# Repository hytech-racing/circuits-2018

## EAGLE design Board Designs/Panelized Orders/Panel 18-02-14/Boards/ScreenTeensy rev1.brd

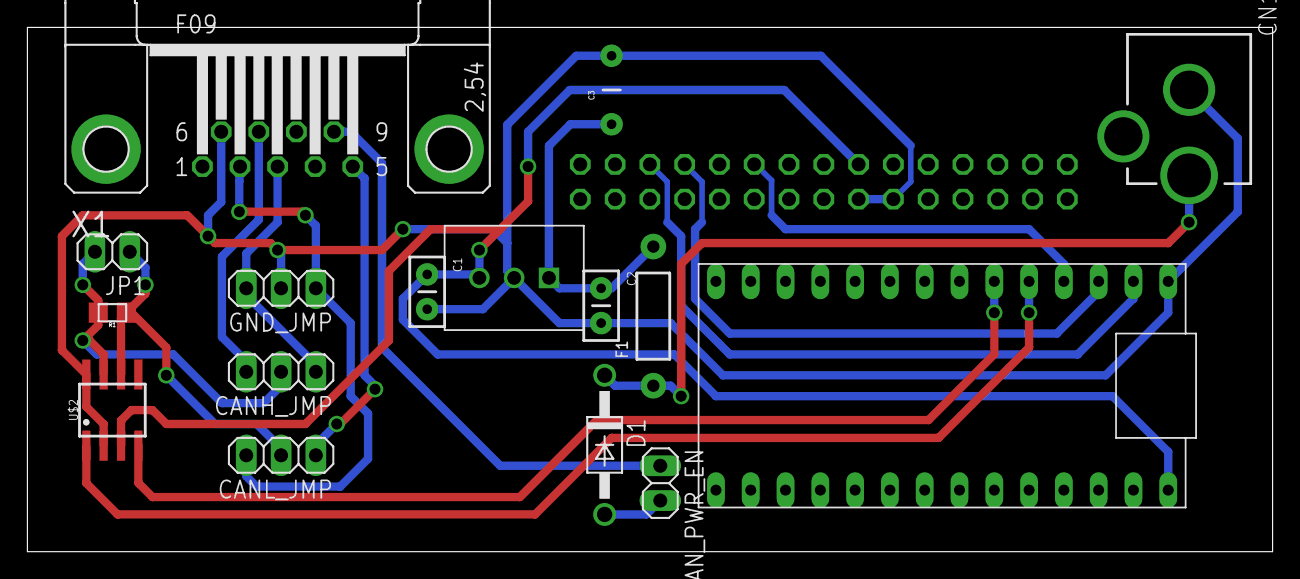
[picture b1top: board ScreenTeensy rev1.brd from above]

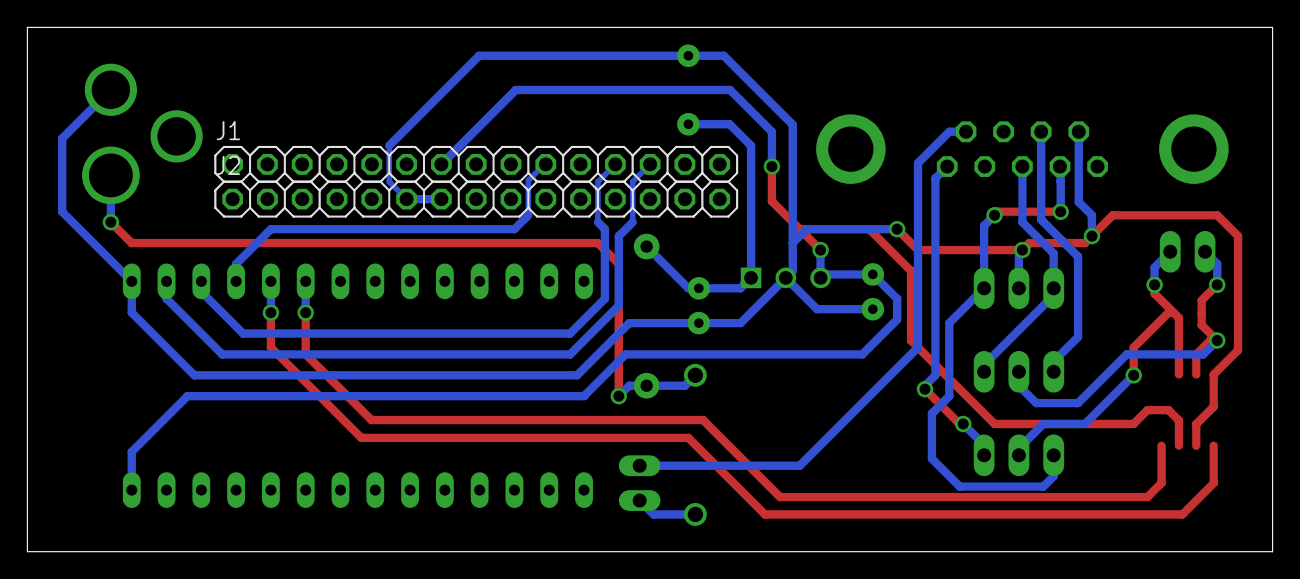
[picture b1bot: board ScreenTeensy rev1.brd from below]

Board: 2 copper layers, 90.9 x 38.3 mm, 18 parts (2 on the bottom side), 17 nets.

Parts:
C1: .1µF; CAP-PTH-SMALLEZ
C2: .33µF; CAP-PTH-SMALLEZ
C3: CAP-PTH-5MM
CANH_JMP: 1X03
CANL_JMP: 1X03
CAN_PWR_EN: 1X02
CN1: DCJACK_2MM_PTH
D1: DIODEDO-41; DO-41
F1: AXIAL-0.4
GND_JMP: 1X03
IC1: TO-220-SPACED
J1, J2: 1X15
JP1: M02; 1X02
R1: 120; 0805
U$1: TEENSY_3.2_SIMPLE
U$2: MCP2551; SOIC-08
X1: F09HP

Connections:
+5V: C1.1, IC1.3, J1.7, U$1.VIN, U$2.3
+12V: C2.1, C3.1, F1.P$2, IC1.1
CANH: CANH_JMP.2, JP1.2, R1.2, U$2.7
CANL: CANL_JMP.2, JP1.1, R1.1, U$2.6
CANRX: U$1.D4(CANRX), U$2.4
CANTX: U$1.D3(CANTX), U$2.1
GND: C1.2, C2.2, C3.2, CN1.GND, GND_JMP.2, IC1.2, J2.6, J2.7, U$1.GND, U$2.2, U$2.8, X1.6
unnamed: CAN_PWR_EN.2, D1.A
unnamed: CAN_PWR_EN.1, X1.9
P2: CANL_JMP.3, GND_JMP.1, X1.2
P3: CANH_JMP.1, GND_JMP.3, X1.3
P5: CANL_JMP.1, X1.5
P7: CANH_JMP.3, X1.7
SCREEN_RS: J1.10, U$1.D2
SCREEN_RX: J1.12, U$1.D1(TX1)
SCREEN_TX: J1.13, U$1.D0(RX1)
V+: CN1.PWR, D1.C, F1.P$1

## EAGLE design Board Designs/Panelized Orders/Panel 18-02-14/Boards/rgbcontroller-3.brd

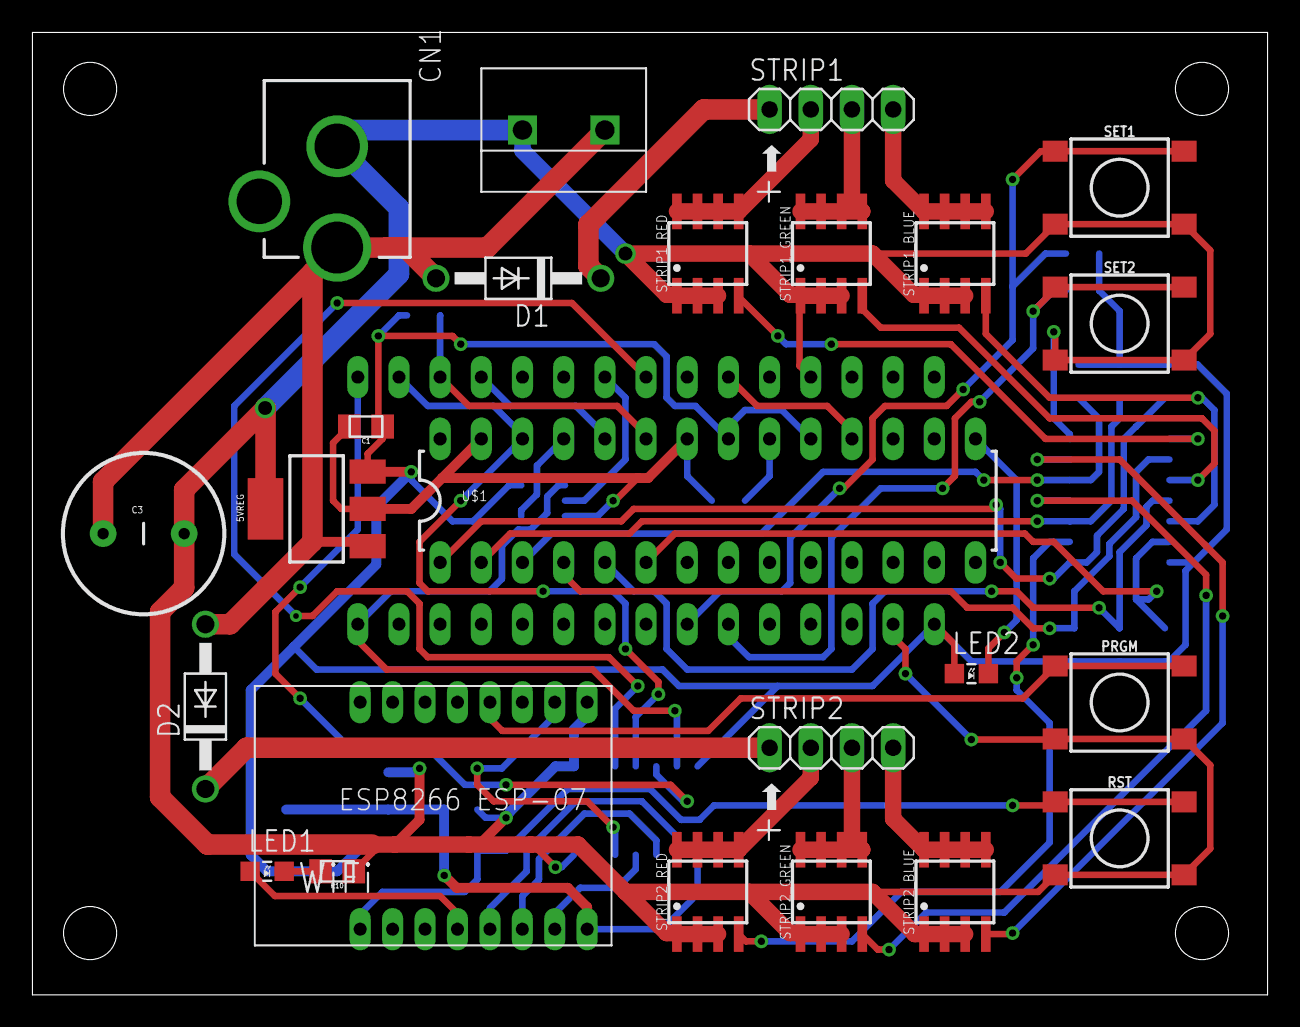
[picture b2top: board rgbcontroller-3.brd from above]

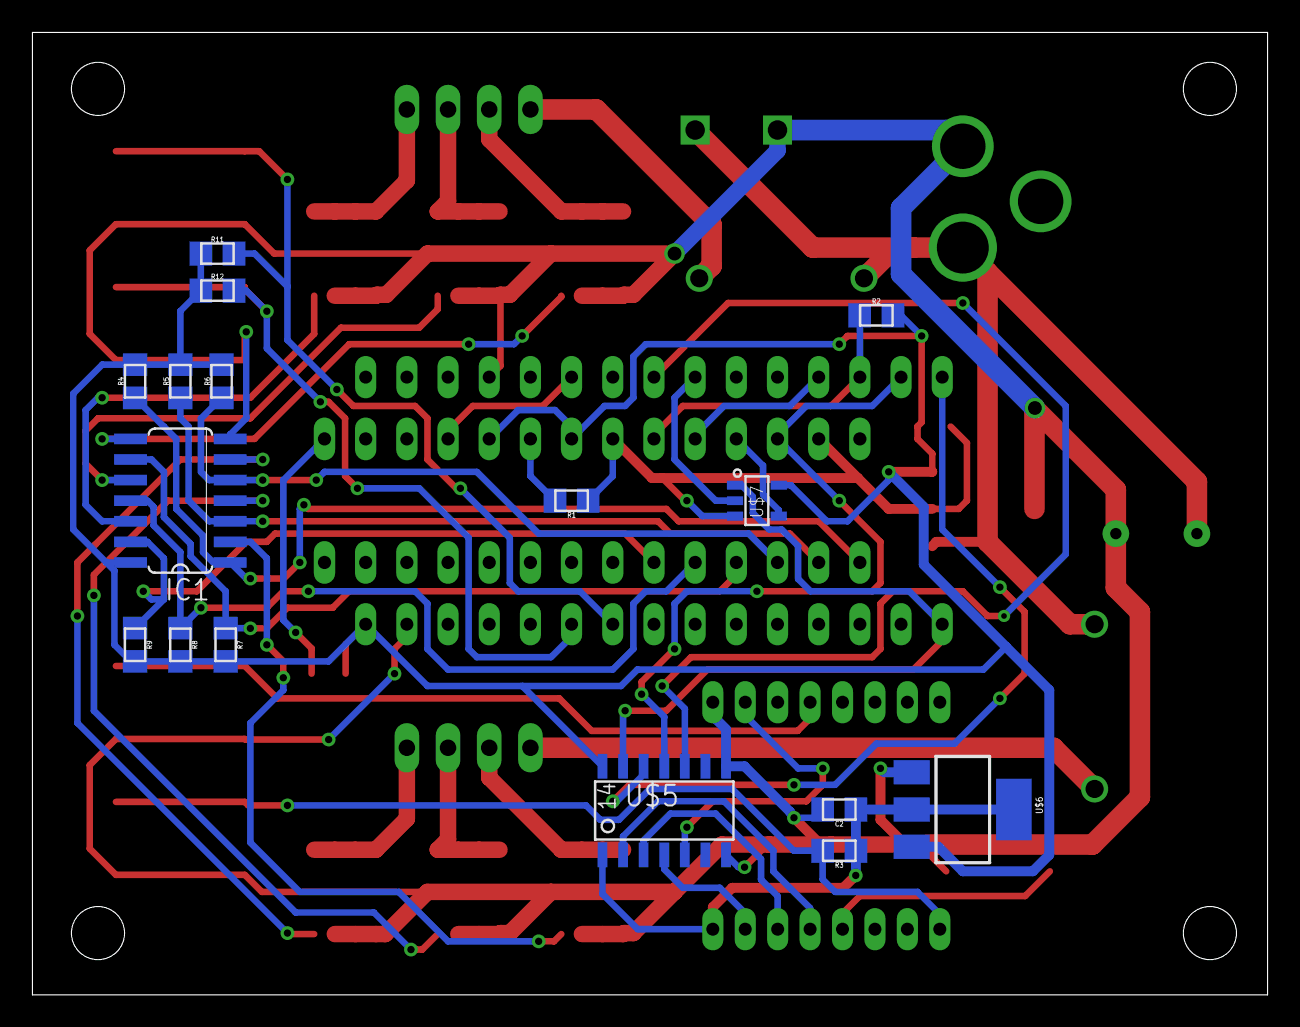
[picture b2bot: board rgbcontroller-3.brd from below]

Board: 2 copper layers, 76.2 x 59.4 mm, 41 parts (16 on the bottom side), 45 nets.

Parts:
5VREG: SOT223
C1: .1µF; 0805
C2: 1µF; 0805
C3: CAP-PTH-5MM
CN1: DCJACK_2MM_PTH
D1, D2: DIODEDO-41; DO-41
IC1: 74HC04D; SO14
LED1: Red; LED-805
LED2: LED-805
PRGM: TACTILE_SWITCH_SMD_6.2MM_TALL
R1: 2.2k; 0805
R2, R3, R4, R5, R6, R7, R8, R9, R11, R12: 10k; 0805
R10: 100; 0805
RST: TACTILE_SWITCH_SMD_6.2MM_TALL
SET1, SET2: TACTILE_SWITCH_SMD_6.2MM_TALL
STRIP1, STRIP2: 1X04
STRIP1_BLUE, STRIP1_GREEN, STRIP1_RED, STRIP2_BLUE, STRIP2_GREEN, STRIP2_RED: MDS1656; SOIC-08
U$1: TLC5940; DIL28-3
U$2: ARDUINO_NANO
U$3: TERMINAL_BLOCK_DG301-02P; DG301-02P
U$4: ESP8266_ESP-07
U$5: SOIC-14
U$6: TLV1117LV33; SOT223
U$7: SN74LVC1G08; SOT-23-5

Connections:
+3V3: C2.1, R3.1, U$4.P$8, U$5.1, U$6.2, U$6.4
+5V: 5VREG.3, C1.1, IC1.14, LED2.A, R2.2, R4.2, R5.2, R6.2, R7.2, R8.2, R9.2, R11.1, R12.1, U$1.19, U$1.21, U$2.VIN, U$5.14, U$6.3, U$7.5
+12V: 5VREG.1, C3.1, CN1.PWR, D1.A, D2.A, U$3.1
BLANK: R2.1, U$1.23, U$2.D10
GND: 5VREG.2, 5VREG.4, C1.2, C2.2, C3.2, CN1.GND, IC1.7, PRGM.A1, PRGM.A2, R1.1, R10.1, RST.A1, RST.A2, SET1.A1, SET1.A2, SET2.A1, SET2.A2, STRIP1_BLUE.1, STRIP1_BLUE.2, STRIP1_BLUE.3, STRIP1_GREEN.1, STRIP1_GREEN.2, STRIP1_GREEN.3, STRIP1_RED.1, STRIP1_RED.2, STRIP1_RED.3, STRIP2_BLUE.1, STRIP2_BLUE.2, STRIP2_BLUE.3, STRIP2_GREEN.1, STRIP2_GREEN.2, STRIP2_GREEN.3, STRIP2_RED.1, STRIP2_RED.2, STRIP2_RED.3, U$1.22, U$1.27, U$2.GND, U$2.GND1, U$3.2, U$4.P$9, U$5.7, U$5.8, U$6.1, U$7.3
MISO: U$2.D12, U$5.12
MISO_33: U$4.P$6, U$5.3
MOSI: U$1.26, U$2.D11, U$5.11
MOSI_33: U$4.P$7, U$5.4
unnamed: STRIP2.2, STRIP2_RED.5, STRIP2_RED.6, STRIP2_RED.7, STRIP2_RED.8
unnamed: STRIP1.2, STRIP1_RED.5, STRIP1_RED.6, STRIP1_RED.7, STRIP1_RED.8
unnamed: IC1.2, STRIP2_RED.4
unnamed: IC1.4, STRIP2_GREEN.4
unnamed: PRGM.B1, PRGM.B2, U$4.P$12
unnamed: R1.2, U$1.20
unnamed: U$1.18, U$2.D3
unnamed: LED1.A, U$4.P$4
unnamed: IC1.8, STRIP1_RED.4
unnamed: IC1.10, STRIP1_GREEN.4
unnamed: IC1.12, STRIP1_BLUE.4
unnamed: IC1.6, STRIP2_BLUE.4
unnamed: IC1.1, R4.1, U$1.1
unnamed: IC1.3, R5.1, U$1.2
unnamed: STRIP1.3, STRIP1_GREEN.5, STRIP1_GREEN.6, STRIP1_GREEN.7, STRIP1_GREEN.8
unnamed: STRIP1.4, STRIP1_BLUE.5, STRIP1_BLUE.6, STRIP1_BLUE.7, STRIP1_BLUE.8
unnamed: STRIP2.3, STRIP2_GREEN.5, STRIP2_GREEN.6, STRIP2_GREEN.7, STRIP2_GREEN.8
unnamed: STRIP2.4, STRIP2_BLUE.5, STRIP2_BLUE.6, STRIP2_BLUE.7, STRIP2_BLUE.8
unnamed: IC1.5, R6.1, U$1.3
unnamed: IC1.13, R9.1, U$1.6
unnamed: R3.2, RST.B1, RST.B2, U$4.P$1
unnamed: IC1.11, R8.1, U$1.5
unnamed: IC1.9, R7.1, U$1.4
unnamed: LED2.C, U$1.15
unnamed: LED1.C, R10.2
unnamed: D1.C, STRIP1.1
unnamed: D2.C, STRIP2.1
SCK: U$2.D13, U$5.13, U$7.1
SCK_33: U$4.P$5, U$5.2
SCK_TLC5940: U$1.25, U$7.4
SET1: R11.2, SET1.B1, SET1.B2, U$2.A5
SET2: R12.2, SET2.B1, SET2.B2, U$2.A6
SS_ESP8266: U$2.D5, U$5.10
SS_ESP8266_33: U$4.P$10, U$5.5
SS_TLC5940: U$2.D6, U$7.2
XLAT: U$1.24, U$2.D9

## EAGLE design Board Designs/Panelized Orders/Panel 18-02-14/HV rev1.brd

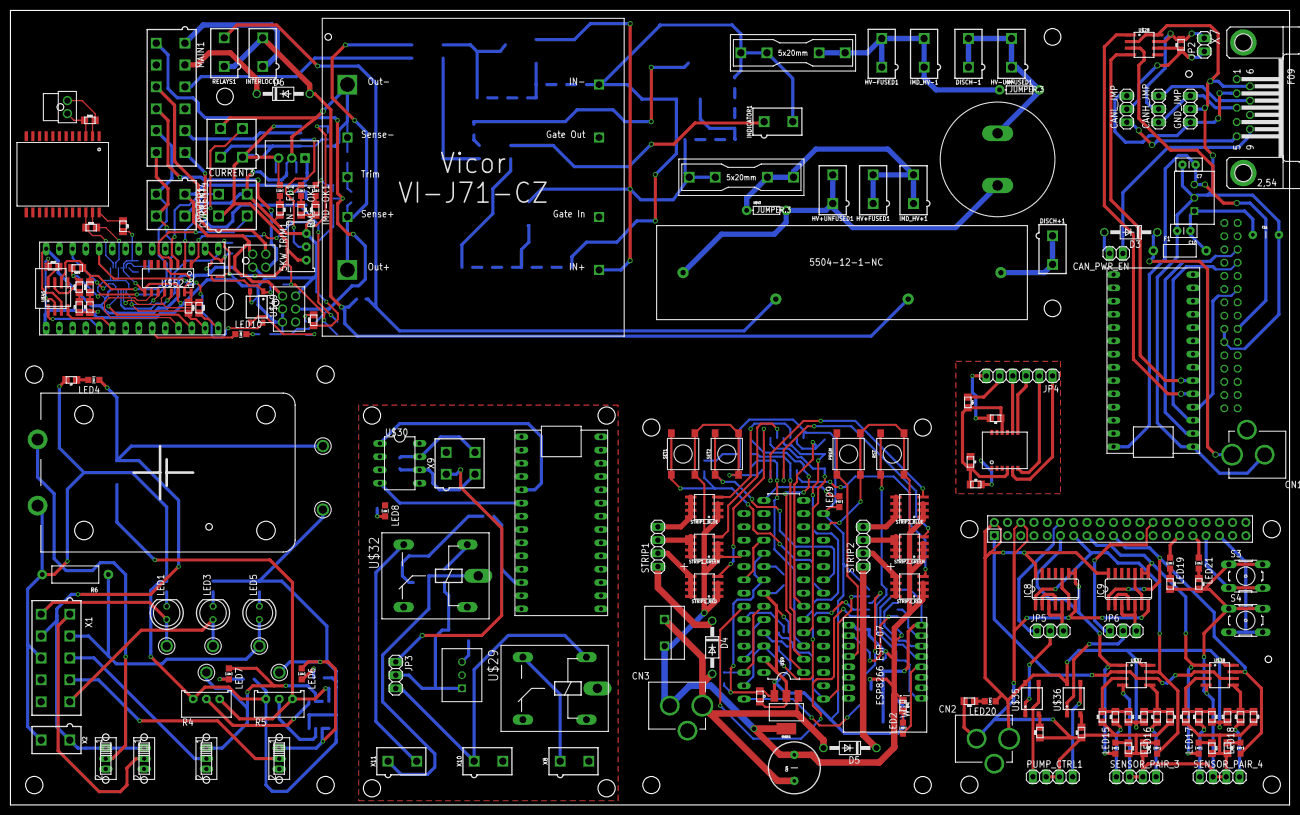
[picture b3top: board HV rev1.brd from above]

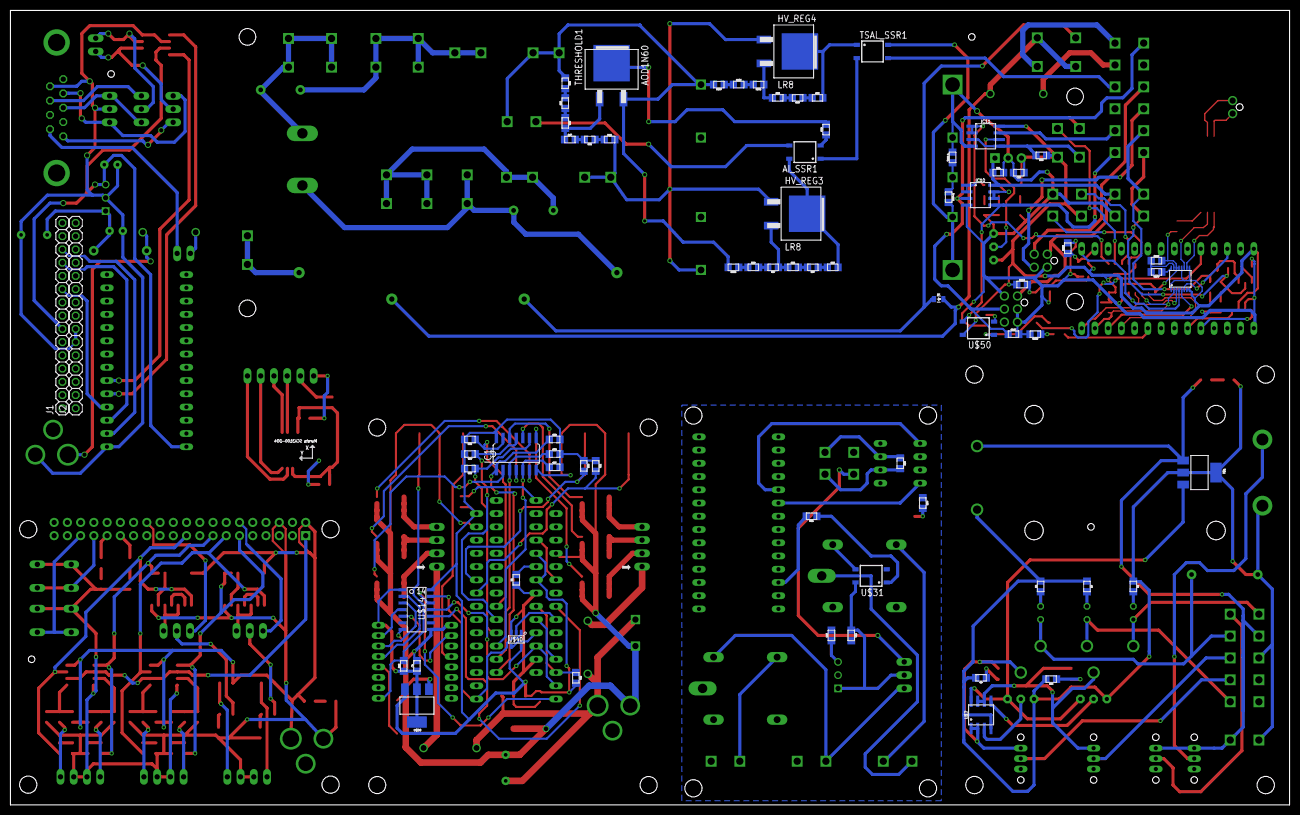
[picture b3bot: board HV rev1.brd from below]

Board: 2 copper layers, 245.4 x 152.4 mm, 249 parts (71 on the bottom side), 226 nets.

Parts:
5KW_TRIM1: TRIMPOT_3296
5VREG: SOT223
9V: 1291-79
AI_SSR1: CPC1002N; SOP04
BMS-OK1: GREEN; LED-805
C2, C8: 100 nF; 0805
C3: .1µF; 0805
C4: 1µF; 0805
C7: .1µF; CAP-PTH-SMALLEZ
C9: 10 uF; 0805
C10: .33µF; CAP-PTH-SMALLEZ
C11, C14: CAP-PTH-5MM
C12: 0.33 uF; 0805
C13: 0.1 uF; 0805
C15, C24: 10uF; 0805
C16, C17, C18, C19: 1µ; 0805
C20: 220uF; LLS2V221MELZ
C21, C22: 560pF; 0805
C23: 27pF; 0805
CANH_JMP: 1X03
CANL_JMP: 1X03
CAN_PWR_EN: 1X02
CN1, CN2, CN3: DCJACK_2MM_PTH
CURRENT3, CURRENT4: CONNECTOR-4; MINIFIT_5566-4
D3, D4, D5: DIODEDO-41; DO-41
D6: DIODE; DO-41
D7: DIODE0805; 0805_D
DISCH+1: DISCHARGE+; MINIFIT_5566-2
DISCH-1: DISCHARGE -; MINIFIT_5566-2
EM1: CONNECTOR-4; NANO-FIT_VERTICAL-4
F1: AXIAL-0.4
FUSE2, FUSE3: 1A; 0751.0110
GND_JMP: 1X03
HV+FUSED1: FUSED+; MINIFIT_5566-2
HV+UNFUSED1: FSAE; MINIFIT_5566-2
HV-FUSED1: FUSED-; MINIFIT_5566-2
HV-UNFUSED1: FSAE; MINIFIT_5566-2
HV_REG3, HV_REG4: LR8; TO-252
IC1: 74HC04D; SO14
IC5, IC6: TO-220-SPACED
IC7: OKI-78SR
IC8, IC9: 4001D; SO14
IC10, IC11: NE5532SOIC; SOIC-08
IMD1: CONNECTOR-6; NANO-FIT_VERTICAL-6
IMD-OK1: YELLOW; LED-805
IMD_HV+1: IMD+; MINIFIT_5566-2
IMD_HV-1: IMD-; MINIFIT_5566-2
INDICATOR1: INDICATOR; MINIFIT_5566-2
INTERLOCK1: MINIFIT_5566-2
ISOSPI1: CONNECTOR-2; NANO-FIT_VERTICAL-2
J1, J2: 1X15
JP2: M02; 1X02
JP3, JP5, JP6: 1X03
JP4: 1X06
LED1: RED; LED-5MM
LED2: Red; LED-805
LED3: GREEN; LED-5MM
LED4, LED8, LED20: PURPLE; LED-805
LED5: BLUE; LED-5MM
LED6, LED15, LED21: RED; LED-805
LED7: YELLOW; LED-805
LED9: LED-805
LED10, LED16: BLUE; LED-805
LED17, LED19: GREEN; LED-805
LED18: ORANGE; LED-805
MAIN1: CONNECTOR-12; MINIFIT_5566-12
ON-LED1: PURPLE; LED-805
POWER1: CONNECTOR-4; MINIFIT_5566-4
PRGM: TACTILE_SWITCH_SMD_6.2MM_TALL
PUMP_CTRL1: 1X04
R1, R9, R10, R69, R75, R86: 270; 0805
R2: 2.2k; 0805
R3, R7, R54, R115: 200; 0805
R4, R5: TRIMPOT_3296
R6: AXIAL-0.5
R8: 680; 0805
R11, R12, R55, R56, R57, R58, R59, R60, R62, R63, R68, R118: 10k; 0805
R14: 10 ohm; 0805
R51, R53, R104, R111: 120; 0805
R52, R76, R77, R78, R79: 330; 0805
R61, R71, R72, R73, R74, R105, R106, R116: 100; 0805
R64, R90, R95, R96, R97, R98, R112, R113, R117: 2k; 0805
R65, R66: 820; 0805
R67, R99, R100: 20k; 0805
R70, R80, R81, R82: 2M; 0805
R83, R84, R85: 150; 0805
R87, R91, R92: 510k; 0805
R88, R93, R94: 43k; 0805
R89, R107, R109, R110: 1k; 0805
R101, R102, R103: 8.2k; 0805
R108: 43; 0805
R114: 430; 0805
RELAYS1: MINIFIT_5566-2
RST: TACTILE_SWITCH_SMD_6.2MM_TALL
S3, S4: B3F-10XX
SENSOR_PAIR_3, SENSOR_PAIR_4: 1X04
SET1, SET2: TACTILE_SWITCH_SMD_6.2MM_TALL
STRIP1, STRIP2: 1X04
STRIP1_BLUE, STRIP1_GREEN, STRIP1_RED, STRIP2_BLUE, STRIP2_GREEN, STRIP2_RED: MDS1656; SOIC-08
SW_INT_BR: 0S102011MS2QS1
SW_INT_CUR: 0S102011MS2QS1
SW_POWER, SW_POWER1: 0S102011MS2QS1
THRESHOLD1: AOD1N60; TO-252
TRIM+1: 0805
TRIM-1: 0805
TSAL_SSR1: CPC1002N; SOP04
U$1: SOT223
U$2, U$3, U$4, U$5, U$6, U$8, U$10: TEST_POINT
U$7, U$37, U$38: MCP6002SOIC; SOIC-08
U$9: TLC5940; DIL28-3
U$11: ARDUINO_NANO
U$12: TERMINAL_BLOCK_DG301-02P; DG301-02P
U$13: ESP8266_ESP-07
U$14: SOIC-14
U$16: SCA3100-D04
U$27, U$33, U$47: TEENSY_3.2_SIMPLE
U$28, U$45: MCP2551; SOIC-08
U$29, U$32: G5LE; ZF112
U$30: MCP2551DIL; DIL08
U$31, U$35, U$36: CPC1002N; SOP04
U$34: RASPBERRY_PI_HEADER
U$39: TLV1117LV33; SOT223
U$40: SN74LVC1G08; SOT-23-5
U$41: 5504-12-1-NC
U$42: HV_DCDC_VI-J71-CZ
U$43, U$44: JUMPER.3; AXIAL-0.3
U$46: LTC6820; MSOP-16
U$48: STWD100; SOT23-5
U$49, U$50: SOP04
U$51: SM51589PEL
U$52: MCP3208SOIC; SOIC-16
X1: CONNECTOR-10; MINIFIT_5566-10
X2, X8, X10, X11: CONNECTOR-2; MINIFIT_5566-2
X7: F09HP
X9: CONNECTOR-4; MINIFIT_5566-4

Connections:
5KW_TRIG1: 5KW_TRIM1.2, IC11.6
!Q3: IC8.2, IC8.4
!Q4: IC9.2, IC9.4
+3V1: C4.1, R12.1, U$13.P$8, U$14.1, U$39.2, U$39.4
+3V2: U$34.1, U$37.2, U$37.6, U$38.2, U$38.6
+3V4: U$46.6, U$47.3.3V
+5V: R4.1, R5.1, U$1.3, U$7.8
+5V1: 5VREG.3, C3.1, IC1.14, LED9.A, R11.2, R55.2, R56.2, R57.2, R58.2, R59.2, R60.2, R62.1, R63.1, U$9.19, U$9.21, U$11.VIN, U$14.14, U$39.3, U$40.5
+5V3: C7.1, IC5.3, J1.7, U$27.VIN, U$28.3
+5V4: C13.1, IC6.3, LED8.A, U$29.P, U$30.3, U$33.VIN
+5V5: CN2.PWR, IC8.14, IC9.14, LED20.A, R70.1, R80.2, R81.1, R82.2, U$34.2, U$35.4, U$36.4, U$37.8, U$38.8
+5V6: 5KW_TRIM1.1, C15.1, CURRENT3.1, CURRENT4.1, IC7.3, IC11.8, ON-LED1.A, R68.1, R112.1, R113.1, R114.1, U$45.3, U$46.1, U$46.7, U$46.8, U$46.9, U$46.12, U$47.VIN, U$48.VCC, U$50.4, U$52.5, U$52.15, U$52.16
+12V: LED4.A, SW_POWER.P$1, SW_POWER1.P$1, U$1.1, U$5.P$1, X1.7, X2.1
+12V1: 5VREG.1, C14.1, CN3.PWR, D4.A, D5.A, U$12.1
+12V3: C10.1, C11.1, F1.P$2, IC5.1
+12V4: C12.1, IC6.1, JP3.2, U$31.4
+12V5: C24.1, EM1.P$1, IC7.1, IC10.8, IMD1.P$1, POWER1.1
BLANK: R11.1, U$9.23, U$11.D10
BMS_OK1: IC10.5, MAIN1.6, U$50.3
BMS_WATCH1: U$49.3, U$50.1
BSPD_CUR_FAULT1: IC11.7, MAIN1.5
BUT3: S3.3, S3.4, U$34.33
BUT4: S4.3, S4.4, U$34.35
CANH1: CANH_JMP.2, JP2.2, R51.2, U$28.7
CANH2: MAIN1.12, POWER1.4, R104.2, R105.2, U$45.7
CANL1: CANL_JMP.2, JP2.1, R51.1, U$28.6
CANL2: MAIN1.11, POWER1.3, R104.1, R106.2, U$45.6
CANRX: U$27.D4(CANRX), U$28.4
CANTX: U$27.D3(CANTX), U$28.1
CHARGE5: C16.2, R76.2, R80.1, U$37.3
CHARGE6: C17.1, R77.2, R81.2, U$37.5
CHARGE7: C18.2, R78.2, R82.1, U$38.3
CHARGE8: C19.1, R70.2, R79.2, U$38.5
CSB1: JP4.1, U$16.CSB
CS_LTC1: U$46.5, U$47.D10(TX2)
CS_MCP1: U$47.D9(RX2), U$52.10
CUR_SENSE_1_RAW1: CURRENT3.2, IC11.3, IC11.5, R68.2
CUR_SENSE_3: CURRENT4.2, U$52.3
CUR_SENSE_4: IC11.1, IC11.2, U$52.1
DISCHARGE_RELAY_GND1: D7.A, RELAYS1.2, U$41.COIL-
EM_IO3: EM1.P$3, MAIN1.9
EM_IO4: EM1.P$4, MAIN1.10
GND: 9V.-, R1.1, R3.1, R4.3, R5.3, R6.P$2, R7.2, R8.2, R9.2, R10.2, U$1.2, U$1.4, U$6.P$1, U$7.4, X1.8, X2.2
GND1: 5VREG.2, 5VREG.4, C3.2, C4.2, C14.2, CN3.GND, IC1.7, PRGM.A1, PRGM.A2, R2.1, R61.1, RST.A1, RST.A2, SET1.A1, SET1.A2, SET2.A1, SET2.A2, STRIP1_BLUE.1, STRIP1_BLUE.2, STRIP1_BLUE.3, STRIP1_GREEN.1, STRIP1_GREEN.2, STRIP1_GREEN.3, STRIP1_RED.1, STRIP1_RED.2, STRIP1_RED.3, STRIP2_BLUE.1, STRIP2_BLUE.2, STRIP2_BLUE.3, STRIP2_GREEN.1, STRIP2_GREEN.2, STRIP2_GREEN.3, STRIP2_RED.1, STRIP2_RED.2, STRIP2_RED.3, U$9.22, U$9.27, U$11.GND, U$11.GND1, U$12.2, U$13.P$9, U$14.7, U$14.8, U$39.1, U$40.3
GND3: C7.2, C10.2, C11.2, CN1.GND, GND_JMP.2, IC5.2, J2.6, J2.7, U$27.GND, U$28.2, U$28.8, X7.6
GND4: C12.2, C13.2, IC6.2, R54.1, U$29.1, U$30.2, U$30.8, U$31.2, U$32.1, U$33.GND, X8.2, X9.2, X10.2
GND5: C16.1, C17.2, C18.1, C19.2, CN2.GND, IC8.7, IC9.7, PUMP_CTRL1.2, PUMP_CTRL1.3, R69.1, R71.2, R72.2, R73.2, R74.2, R75.1, R83.2, R84.2, R85.2, S3.1, S3.2, S4.1, S4.2, SENSOR_PAIR_3.2, SENSOR_PAIR_3.3, SENSOR_PAIR_4.2, SENSOR_PAIR_4.3, U$34.6, U$37.4, U$38.4
GND6: 5KW_TRIM1.3, C15.2, C21.1, C22.1, C23.2, C24.2, CURRENT3.4, CURRENT4.4, EM1.P$2, IC7.2, IC10.4, IC11.4, IMD1.P$2, IMD1.P$3, IMD1.P$4, POWER1.2, R65.1, R66.2, R86.2, R107.1, R108.2, R110.2, R115.1, R117.2, R118.2, TRIM-1.2, U$42.8SENSE-, U$42.9VOUT-, U$45.2, U$46.13, U$46.14, U$47.GND, U$48.EN, U$48.GND, U$49.2, U$52.9, U$52.14
GND7: C2.1, C8.2, C9.2, JP4.6, U$16.AVSS, U$16.DVSS, U$16.EGND, U$16.NC1, U$16.NC2
HV+FUSED1: FUSE2.L1, FUSE2.L2, HV+FUSED1.1, HV+FUSED1.2, IMD_HV+1.1, IMD_HV+1.2, U$43.P$1
HV+FUSED_1A1: FUSE2.R1, FUSE2.R2, HV_REG3.1, HV_REG4.1, R92.2, U$42.1VIN+
HV+UNFUSED_FSAE1: C20.P$1, HV+UNFUSED1.1, HV+UNFUSED1.2, U$41.CONTACT1, U$43.P$2
HV+UNFUSED_FSAE_DISCHARGE1: DISCH+1.1, DISCH+1.2, U$41.CONTACT2
HV-FUSED1: FUSE3.L1, FUSE3.L2, HV-FUSED1.1, HV-FUSED1.2, IMD_HV-1.1, IMD_HV-1.2, U$44.P$1
HV-FUSED_1A1: FUSE3.R1, FUSE3.R2, INDICATOR1.2, R88.1, R100.2, R103.2, THRESHOLD1.3, U$42.4VIN-
HV-UNFUSED_FSAE1: C20.P$2, DISCH-1.1, DISCH-1.2, HV-UNFUSED1.1, HV-UNFUSED1.2, U$44.P$2
ISOSPI-M1: ISOSPI1.P$2, R116.1, U$51.3
ISOSPI-P1: ISOSPI1.P$1, R116.2, U$51.2
LED3: LED21.A, U$34.31
LED4: LED19.A, U$34.29
MISO1: U$11.D12, U$14.12
MISO2: R113.2, U$46.3, U$47.D12, U$52.12
MISO3: JP4.2, U$16.MISO
MISO_33: U$13.P$6, U$14.3
MOSI1: U$9.26, U$11.D11, U$14.11
MOSI2: R112.2, U$46.2, U$47.D11, U$52.11
MOSI3: JP4.4, U$16.MOSI
MOSI_33: U$13.P$7, U$14.4
unnamed: LED1.K, R1.2
unnamed: R2.2, U$9.20
unnamed: LED3.K, R3.2
unnamed: R4.2, U$7.5
unnamed: R5.2, U$7.3
unnamed: 9V.+, SW_POWER.P$2
unnamed: LED4.C, R7.1
unnamed: LED6.A, SW_INT_BR.P$1, U$3.P$1, U$7.1, U$7.2
unnamed: LED7.A, SW_INT_CUR.P$1, U$2.P$1, U$7.6, U$7.7
unnamed: LED6.C, R9.1
unnamed: LED5.K, R8.1
unnamed: LED7.C, R10.1
unnamed: SW_POWER1.P$2, X1.1
unnamed: U$9.18, U$11.D3
unnamed: STRIP2.2, STRIP2_RED.5, STRIP2_RED.6, STRIP2_RED.7, STRIP2_RED.8
unnamed: STRIP1.2, STRIP1_RED.5, STRIP1_RED.6, STRIP1_RED.7, STRIP1_RED.8
unnamed: STRIP1.3, STRIP1_GREEN.5, STRIP1_GREEN.6, STRIP1_GREEN.7, STRIP1_GREEN.8
unnamed: STRIP1.4, STRIP1_BLUE.5, STRIP1_BLUE.6, STRIP1_BLUE.7, STRIP1_BLUE.8
unnamed: STRIP2.3, STRIP2_GREEN.5, STRIP2_GREEN.6, STRIP2_GREEN.7, STRIP2_GREEN.8
unnamed: STRIP2.4, STRIP2_BLUE.5, STRIP2_BLUE.6, STRIP2_BLUE.7, STRIP2_BLUE.8
unnamed: R12.2, RST.B1, RST.B2, U$13.P$1
unnamed: IC1.2, STRIP2_RED.4
unnamed: IC1.4, STRIP2_GREEN.4
unnamed: IC1.8, STRIP1_RED.4
unnamed: IC1.10, STRIP1_GREEN.4
unnamed: C2.2, C8.1, C9.1, R14.2, U$16.AVDD, U$16.DVDD
unnamed: CAN_PWR_EN.1, X7.9
unnamed: CAN_PWR_EN.2, D3.A
unnamed: R53.2, U$30.6, X9.3
unnamed: U$30.4, U$33.D4(CANRX)
unnamed: U$30.1, U$33.D3(CANTX)
unnamed: R52.2, U$33.D10(TX2)
unnamed: R52.1, U$31.1
unnamed: U$31.3, U$32.2
unnamed: U$32.P, X11.1
unnamed: U$32.S, X11.2
unnamed: JP3.3, U$29.2, X10.1
unnamed: JP3.1, X9.1
unnamed: R53.1, U$30.7, X9.4
unnamed: U$29.S, X8.1
unnamed: LED8.C, R54.2
unnamed: IC1.12, STRIP1_BLUE.4
unnamed: IC1.6, STRIP2_BLUE.4
unnamed: R69.2, U$35.2
unnamed: R75.2, U$36.2
unnamed: PUMP_CTRL1.1, U$35.3
unnamed: PUMP_CTRL1.4, U$36.3
unnamed: R78.1, SENSOR_PAIR_4.1
unnamed: R79.1, SENSOR_PAIR_4.4
unnamed: R77.1, SENSOR_PAIR_3.4
unnamed: R76.1, SENSOR_PAIR_3.1
unnamed: LED15.C, R71.1
unnamed: LED16.C, R72.1
unnamed: LED17.C, R73.1
unnamed: LED18.C, R74.1
unnamed: LED19.C, R83.1
unnamed: LED20.C, R84.1
unnamed: LED21.C, R85.1
unnamed: IC1.1, R55.1, U$9.1
unnamed: IC1.3, R56.1, U$9.2
unnamed: IC1.5, R57.1, U$9.3
unnamed: IC1.13, R60.1, U$9.6
unnamed: IC1.11, R59.1, U$9.5
unnamed: IC1.9, R58.1, U$9.4
unnamed: PRGM.B1, PRGM.B2, U$13.P$12
unnamed: LED2.A, U$13.P$4
unnamed: LED9.C, U$9.15
unnamed: LED2.C, R61.2
unnamed: D4.C, STRIP1.1
unnamed: D5.C, STRIP2.1
unnamed: AI_SSR1.4, HV_REG3.2(TAB), R98.2
unnamed: HV_REG3.3, R64.1, R67.1
unnamed: IC10.1, IC10.2, IMD-OK1.A
unnamed: BMS-OK1.A, IC10.6, IC10.7
unnamed: BMS-OK1.C, R66.1
unnamed: IMD-OK1.C, R65.2
unnamed: ON-LED1.C, R86.1
unnamed: HV_REG4.2(TAB), R90.2, TSAL_SSR1.1
unnamed: R91.1, R92.1
unnamed: R87.2, R91.2
unnamed: R93.1, R94.1
unnamed: R88.2, R93.2
unnamed: AI_SSR1.2, R89.1
unnamed: AI_SSR1.1, TSAL_SSR1.2
unnamed: AI_SSR1.3, INDICATOR1.1
unnamed: HV_REG4.3, R96.1, R101.1
unnamed: R101.2, R102.2
unnamed: R102.1, R103.1
unnamed: R87.1, R94.2, THRESHOLD1.1
unnamed: R95.2, R96.2
unnamed: R90.1, R95.1
unnamed: R89.2, THRESHOLD1.2(TAB)
unnamed: R64.2, R97.2
unnamed: R97.1, R98.1
unnamed: R67.2, R99.2
unnamed: R99.1, R100.1
unnamed: U$45.1, U$47.D3(CANTX)
unnamed: R107.2, U$45.8
unnamed: C21.2, R105.1
unnamed: C22.2, R106.1
unnamed: LED10.C, R108.1
unnamed: R109.1, U$46.16
unnamed: R109.2, R110.1, U$46.15
unnamed: R111.1, U$46.10, U$51.22
unnamed: R111.2, U$46.11, U$51.23
unnamed: C23.1, U$51.24
unnamed: U$45.4, U$47.D4(CANRX)
unnamed: LED10.A, U$47.D7(RX3)
unnamed: R114.2, U$48.WDO, U$49.1
unnamed: U$47.A8, U$49.4
unnamed: R118.1, U$47.A0, U$48.WDI
unnamed: R115.2, U$50.2
OKHS1: IC10.3, IMD1.P$5, MAIN1.7, R117.1
P2: CANL_JMP.3, GND_JMP.1, X7.2
P3: CANH_JMP.1, GND_JMP.3, X7.3
P5: CANL_JMP.1, X7.5
P7: CANH_JMP.3, X7.7
PI_PUMP_CTRL3: JP6.1, U$34.26
PI_PUMP_CTRL4: JP5.1, U$34.12
PUMP_CTRL3: JP5.2, U$35.1
PUMP_CTRL4: JP6.2, U$36.1
Q3: IC8.3, IC8.5, JP5.3
Q4: IC9.3, IC9.5, JP6.3
READ_FAULT: LED3.A, U$8.P$1, X1.5
READ_SWITCH: LED1.A, U$10.P$1, X1.6
S5: IC8.1, LED16.A, U$34.13, U$37.7
S6: IC8.8, IC8.9, LED15.A, U$34.11, U$37.1
S7: IC9.8, IC9.9, LED17.A, U$34.15, U$38.1
S8: IC9.1, LED18.A, U$34.19, U$38.7
SCK1: U$11.D13, U$14.13, U$40.1
SCK2: U$46.4, U$47.D13, U$52.13
SCK3: JP4.3, U$16.SCK
SCK_33: U$13.P$5, U$14.2
SCK_TLC5940: U$9.25, U$40.4
SCREEN_RS: J1.10, U$27.D2
SCREEN_RX: J1.12, U$27.D1(TX1)
SCREEN_TX: J1.13, U$27.D0(RX1)
SET1: R62.2, SET1.B1, SET1.B2, U$11.A5
SET2: R63.2, SET2.B1, SET2.B2, U$11.A6
SET_P1_ON1: IC8.6, IC8.10
SET_P2_ON1: IC9.6, IC9.10
SHUTDOWN1: D6.A, D7.C, INTERLOCK1.2, RELAYS1.1, U$41.COIL+
SHUTDOWN2: INTERLOCK1.1, MAIN1.1
SHUTDOWN7_EXT_OUT1: D6.C, MAIN1.2
SHUTDOWN_D: LED5.A, R6.P$1, U$4.P$1, X1.2
SIGNAL_BRAKE: SW_INT_BR.P$2, X1.4
SIGNAL_CURRENT: SW_INT_CUR.P$2, X1.3
SS_ESP8266: U$11.D5, U$14.10
SS_ESP8266_33: U$13.P$10, U$14.5
SS_TLC5940: U$11.D6, U$40.2
TEMP_SENSE_3: CURRENT4.3, U$52.4
TEMP_SENSE_4: CURRENT3.3, U$52.2
TRIM1: TRIM+1.1, TRIM-1.1, U$42.7TRIM
TSAL+1: MAIN1.3, TSAL_SSR1.3
TSAL_2: TRIM+1.2, TSAL_SSR1.4, U$42.5VOUT+, U$42.6SENSE+
V+: CN1.PWR, D3.C, F1.P$1
VDD1: JP4.5, R14.1
XLAT: U$9.24, U$11.D9
